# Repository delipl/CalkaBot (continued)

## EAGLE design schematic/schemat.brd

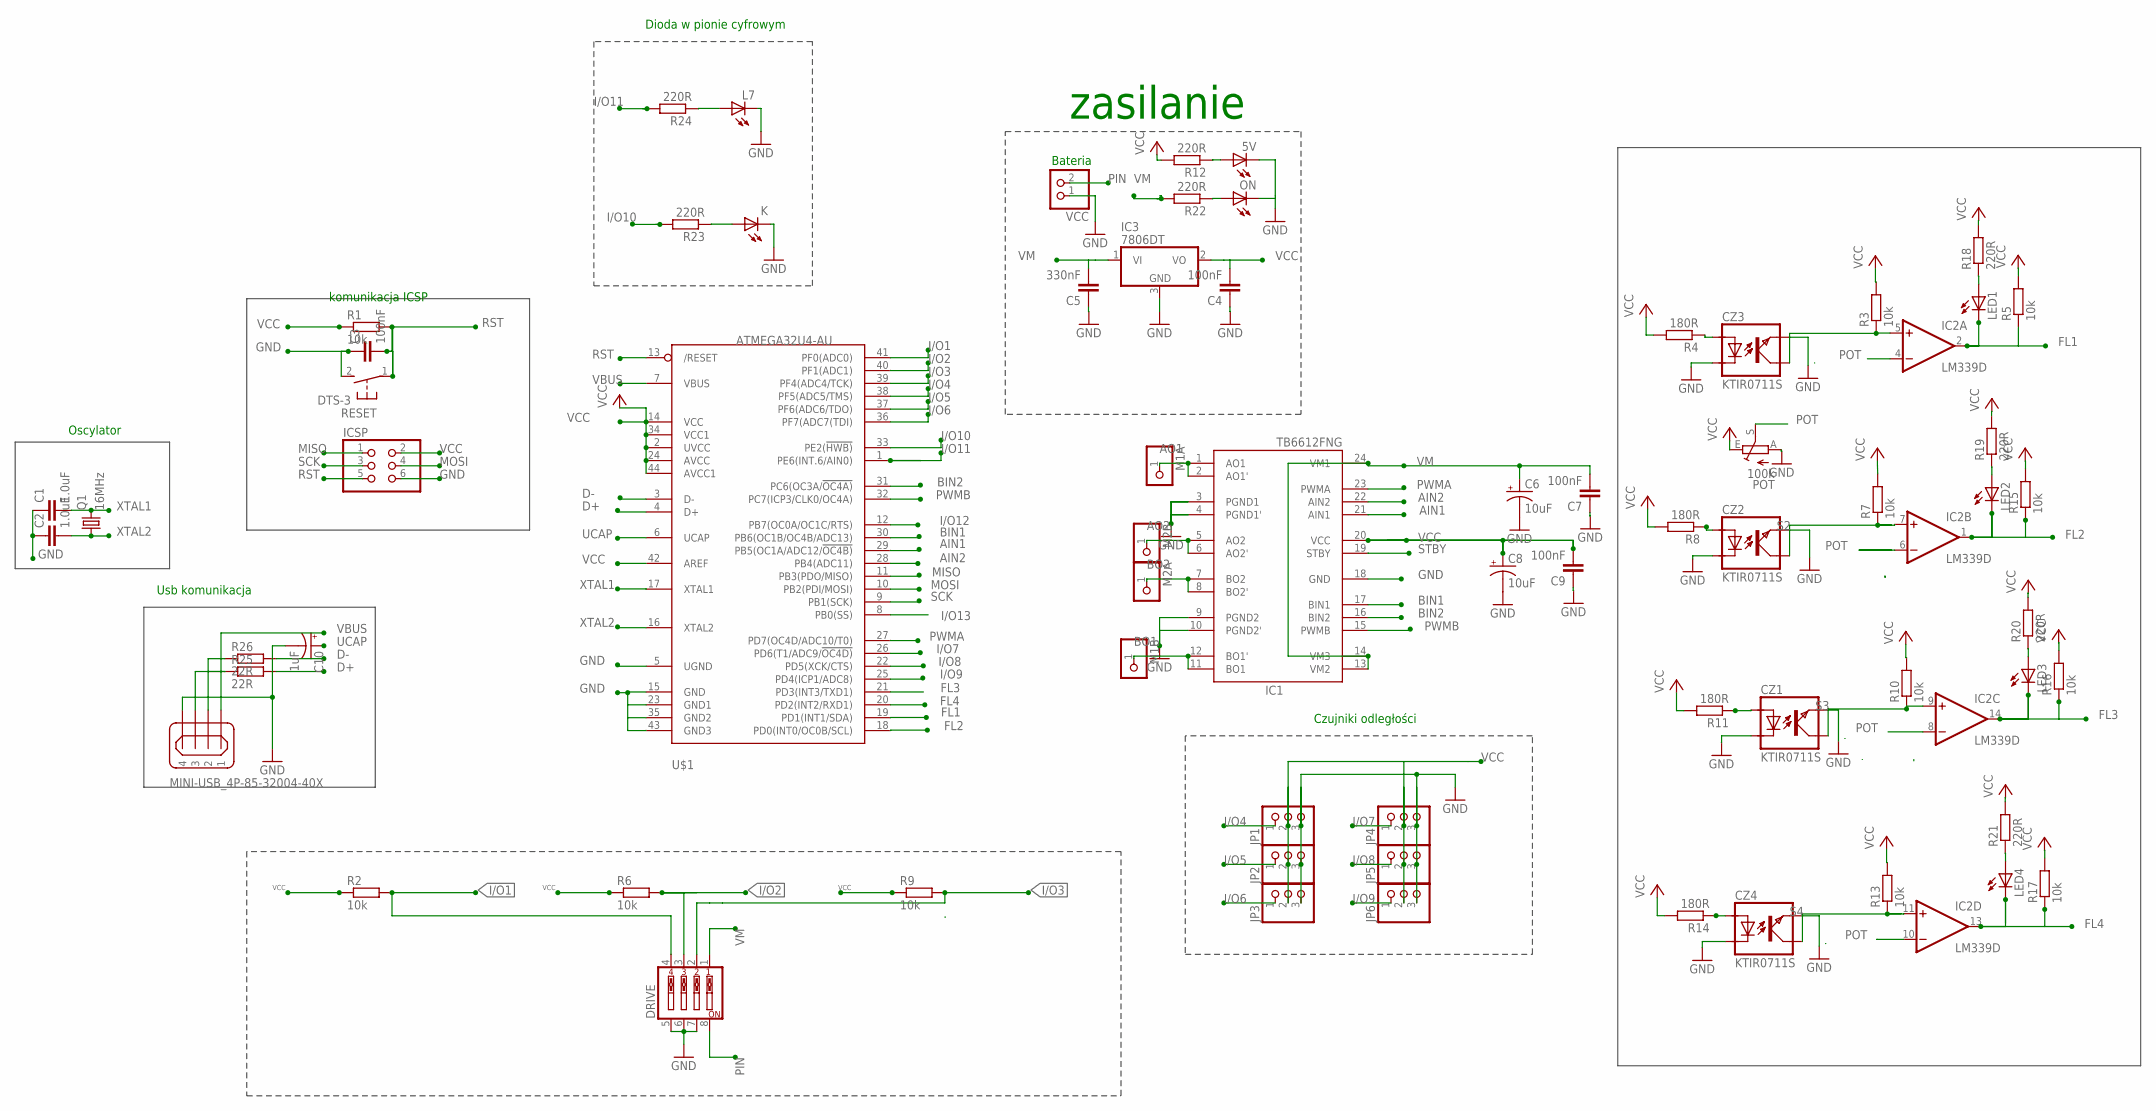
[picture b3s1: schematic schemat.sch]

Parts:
5V: LEDCHIP-LED0805; CHIP-LED0805
C1, C2: 1.0uF; C0805
C3, C4, C7, C9: 100nF; C0805
C5: 330nF; C0805
C6, C8: 10uF; UD-4X5,8_NICHICON
C10: 1uF; UD-4X5,8_NICHICON
CZ1, CZ2, CZ3, CZ4: KTIR0711S; TOP
DRIVE: SW_DIP-4; EDG-04
IC1: TB6612FNG; SSOP24
IC2: LM339D; SO14
IC3: 7806DT; TO252
ICSP: PINHD-2X3; 2X03
JP1, JP2, JP3, JP4, JP5, JP6: PINHD-1X3; 1X03
K: LEDCHIP-LED0805; CHIP-LED0805
L7: LEDCHIP-LED0805; CHIP-LED0805
LED1, LED2, LED3, LED4: LEDCHIP-LED0805; CHIP-LED0805
M1A, M1B, M2A, M2B: PINHD-1X1; 1X01
ON: LEDCHIP-LED0805; CHIP-LED0805
POT: 100k; CA6V
Q1: 16MHz; CSM-7X-DU
R1, R2, R3, R5, R6, R7, R9, R10, R13, R15, R16, R17: 10k; R0805
R4, R8, R11, R14: 180R; R0805
R12, R18, R19, R20, R21, R22, R23, R24: 220R; R0805
R25, R26: 22R; R0805
RESET: DTS-3
U$1: ATMEGA32U4-AU; TQFP44
USB: MINI-USB_4P-85-32004-40X; 85-32004-40X
VCC: PINHD-1X2; 1X02

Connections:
AIN1: IC1.21 (AIN1), U$1.29 (PB5(OC1A/ADC12/!OC4B))
AIN2: IC1.22 (AIN2), U$1.28 (PB4(ADC11))
AO1: IC1.1 (AO1), IC1.2 (AO1'), M1A.1
AO2: IC1.5 (AO2), IC1.6 (AO2'), M2B.1
BIN1: IC1.17 (BIN1), U$1.30 (PB6(OC1B/OC4B/ADC13))
BIN2: IC1.16 (BIN2), U$1.31 (PC6(OC3A/!OC4A))
BO1: IC1.11 (BO1), IC1.12 (BO1'), M1B.1
BO2: IC1.7 (BO2), IC1.8 (BO2'), M2A.1
D+: R25.2, U$1.4 (D+)
D-: R26.2, U$1.3 (D-)
FL1: IC2.2 (OUT), LED1.C, R5.1, U$1.19 (PD1(INT1/SDA))
FL2: IC2.1 (OUT), LED2.C, R15.1, U$1.18 (PD0(INT0/OC0B/SCL))
FL3: IC2.14 (OUT), LED3.C, R16.1, U$1.21 (PD3(INT3/TXD1))
FL4: IC2.13 (OUT), LED4.C, R17.1, U$1.20 (PD2(INT2/RXD1))
GND: 5V.C, C1.1, C2.1, C3.1, C4.1, C5.1, C6.-, C7.1, C8.-, C9.1, C10.-, CZ1.EMITER, CZ1.KATODA, CZ2.EMITER, CZ2.KATODA, CZ3.EMITER, CZ3.KATODA, CZ4.EMITER, CZ4.KATODA, DRIVE.5, DRIVE.6, DRIVE.7, IC1.3 (PGND1), IC1.4 (PGND1'), IC1.9 (PGND2), IC1.10 (PGND2'), IC1.18 (GND), IC2.12 (GND), IC3.3 (GND), ICSP.6, JP1.3, JP2.3, JP3.3, JP4.3, JP5.3, JP6.3, K.C, L7.C, ON.C, POT.A, RESET.2, U$1.5 (UGND), U$1.15 (GND), U$1.23 (GND1), U$1.35 (GND2), U$1.43 (GND3), USB.4, VCC.1
I/O1: DRIVE.4, R2.2, U$1.41 (PF0(ADC0))
I/O2: DRIVE.3, R6.2, U$1.40 (PF1(ADC1))
I/O3: DRIVE.2, R9.2, U$1.39 (PF4(ADC4/TCK))
I/O4: JP1.1, U$1.38 (PF5(ADC5/TMS))
I/O5: JP2.1, U$1.37 (PF6(ADC6/TDO))
I/O6: JP3.1, U$1.36 (PF7(ADC7(TDI))
I/O7: JP4.1, U$1.26 (PD6(T1/ADC9/!OC4D))
I/O8: JP5.1, U$1.22 (PD5(XCK/CTS))
I/O9: JP6.1, U$1.25 (PD4(ICP1/ADC8))
I/O10: R23.2, U$1.33 (PE2(!HWB))
I/O11: R24.2, U$1.1 (PE6(INT.6/AIN0))
I/O12: U$1.12 (PB7(OC0A/OC1C/RTS))
I/O13: U$1.8 (PB0(SS))
MISO: ICSP.1, U$1.11 (PB3(PDO/MISO))
MOSI: ICSP.4, U$1.10 (PB2(PDI/MOSI))
unnamed: CZ3.KOLEKTOR, IC2.5 (+IN), R3.1
unnamed: K.A, R23.1
unnamed: 5V.A, R12.1
unnamed: ON.A, R22.1
unnamed: R26.1, USB.2
unnamed: R25.1, USB.3
unnamed: LED1.A, R18.1
unnamed: CZ3.ANODA, R4.1
unnamed: LED2.A, R19.1
unnamed: LED3.A, R20.1
unnamed: LED4.A, R21.1
unnamed: L7.A, R24.1
unnamed: CZ2.ANODA, R8.1
unnamed: CZ1.ANODA, R11.1
unnamed: CZ4.ANODA, R14.1
PIN: DRIVE.8, VCC.2
POT: IC2.4 (-IN), IC2.6 (-IN), IC2.8 (-IN), IC2.10 (-IN), POT.S
PWMA: IC1.23 (PWMA), U$1.27 (PD7(OC4D/ADC10/T0))
PWMB: IC1.15 (PWMB), U$1.32 (PC7(ICP3/CLK0/OC4A))
RST: C3.2, ICSP.5, R1.2, RESET.1, U$1.13 (/RESET)
S2: CZ2.KOLEKTOR, IC2.7 (+IN), R7.1
S3: CZ1.KOLEKTOR, IC2.9 (+IN), R10.1
S4: CZ4.KOLEKTOR, IC2.11 (+IN), R13.1
SCK: ICSP.3, U$1.9 (PB1(SCK))
STBY: IC1.19 (STBY)
UCAP: C10.+, U$1.6 (UCAP)
VBUS: U$1.7 (VBUS), USB.1
VCC: C4.2, C8.+, C9.2, IC1.20 (VCC), IC2.3 (V+), IC3.2 (VO), ICSP.2, JP1.2, JP2.2, JP3.2, JP4.2, JP5.2, JP6.2, POT.E, R1.1, R2.1, R3.2, R4.2, R5.2, R6.1, R7.2, R8.2, R9.1, R10.2, R11.2, R12.2, R13.2, R14.2, R15.2, R16.2, R17.2, R18.2, R19.2, R20.2, R21.2, U$1.2 (UVCC), U$1.14 (VCC), U$1.24 (AVCC), U$1.34 (VCC1), U$1.42 (AREF), U$1.44 (AVCC1)
VM: C5.2, C6.+, C7.2, DRIVE.1, IC1.13 (VM2), IC1.14 (VM3), IC1.24 (VM1), IC3.1 (VI), R22.2
XTAL1: C1.2, Q1.2, U$1.17 (XTAL1)
XTAL2: C2.2, Q1.1, U$1.16 (XTAL2)

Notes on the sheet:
Oscylator
Usb komunikacja
komunikacja ICSP
Bateria
zasilanie
Dioda w pionie cyfrowym
Czujniki odległości

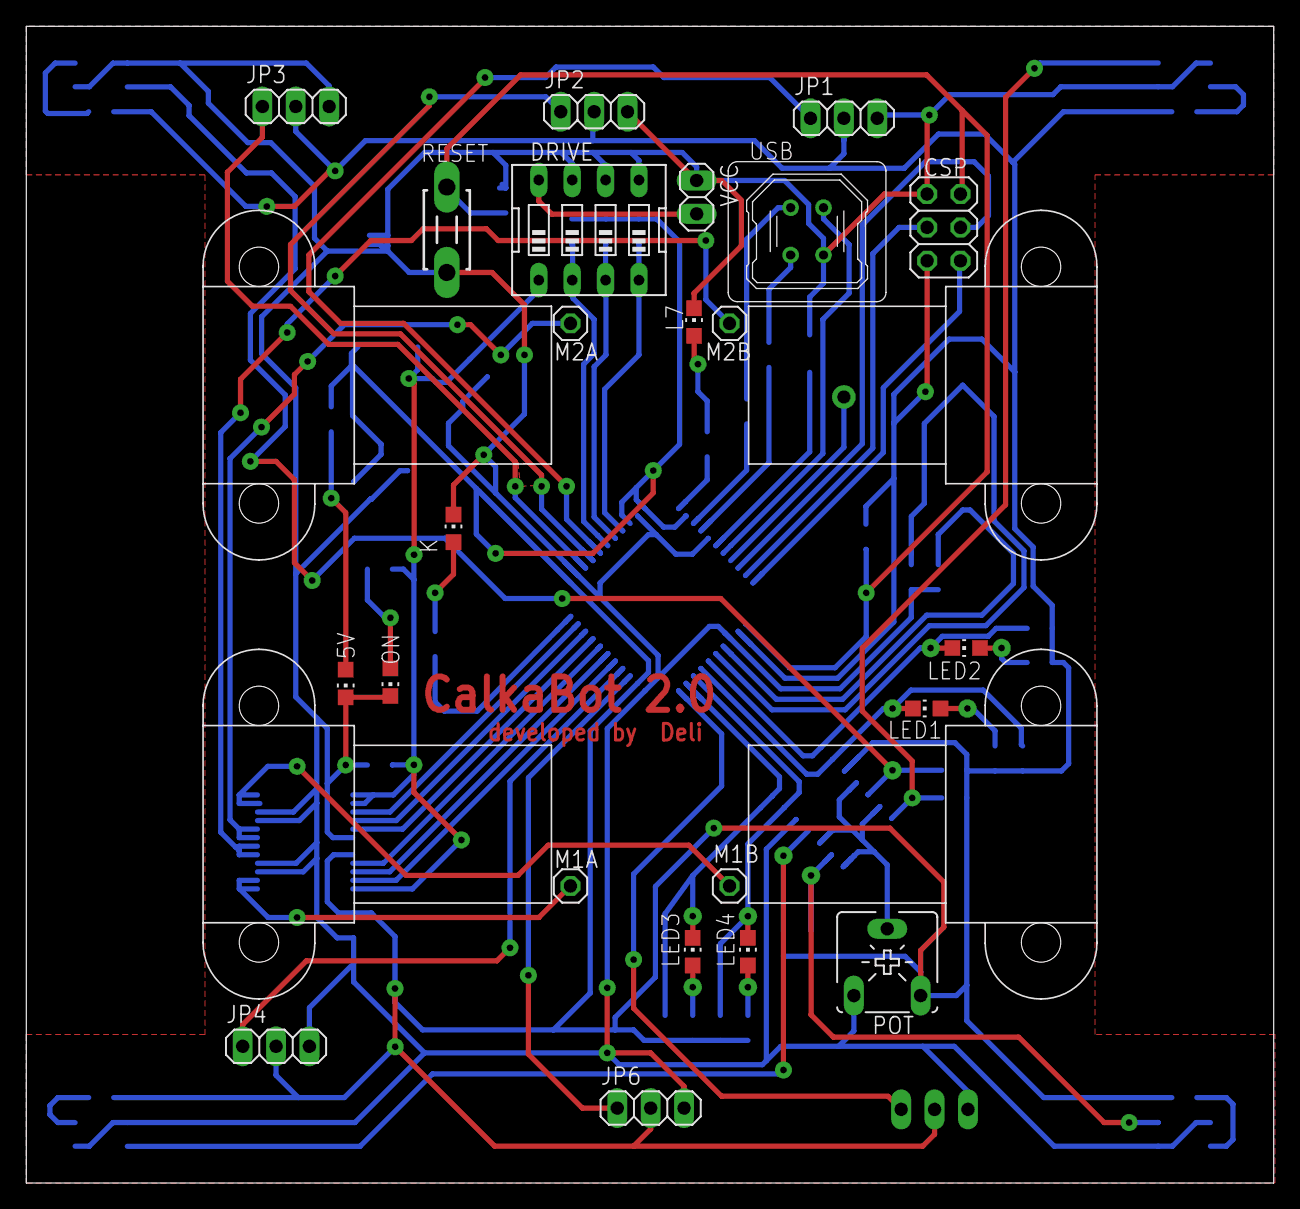
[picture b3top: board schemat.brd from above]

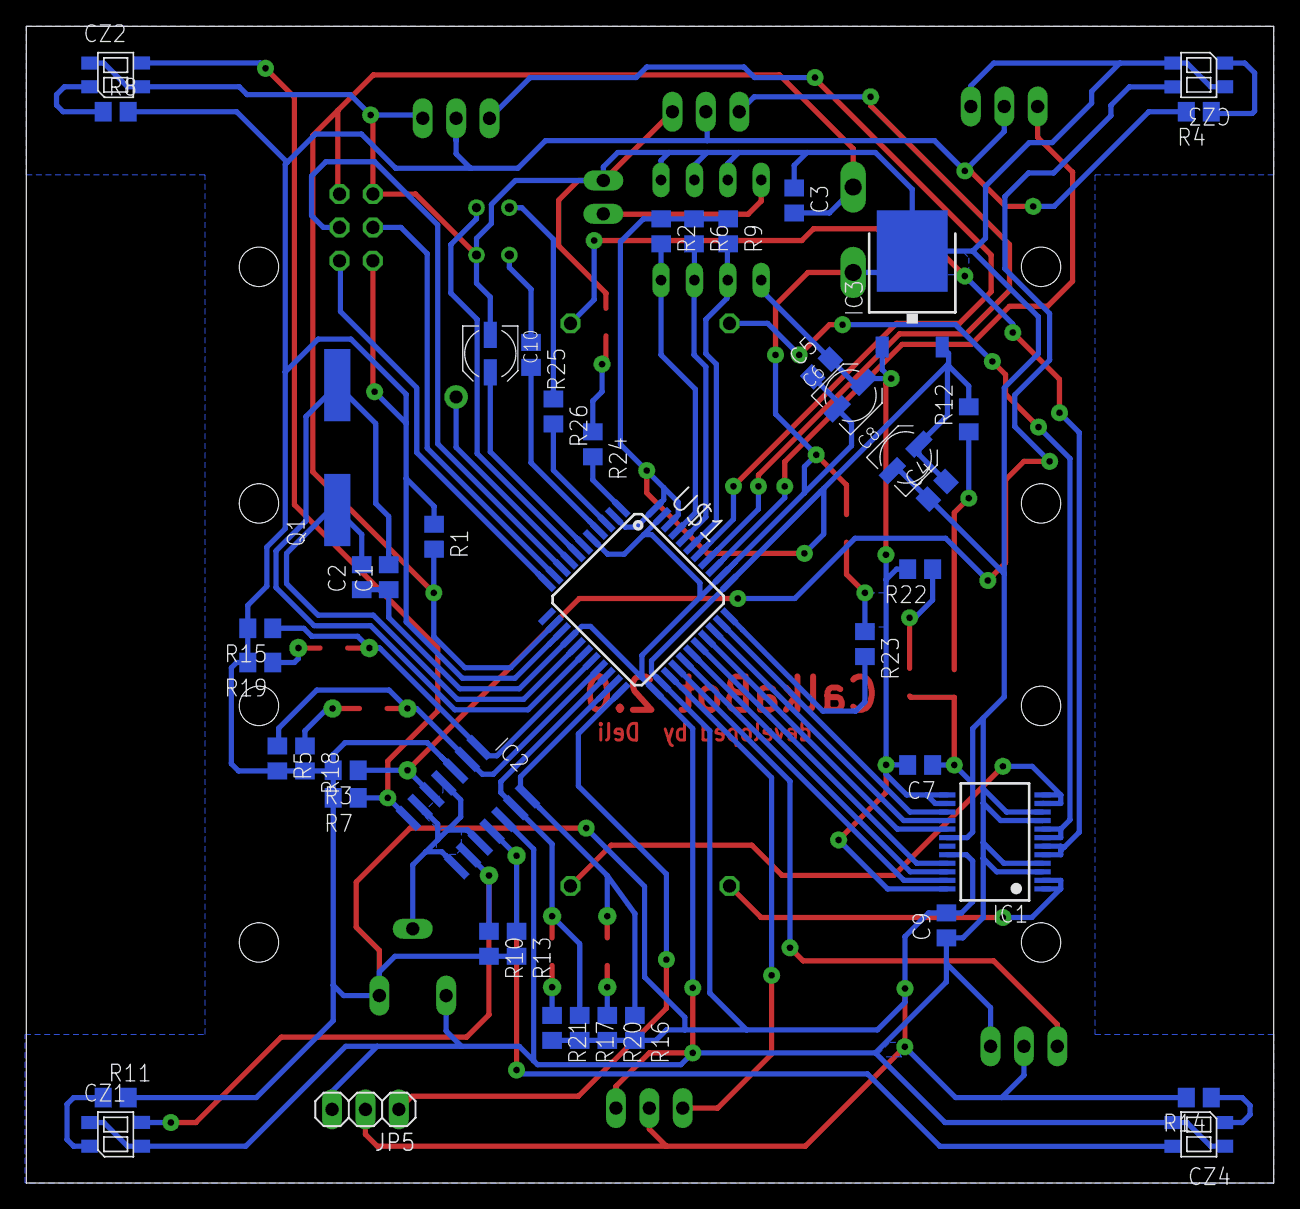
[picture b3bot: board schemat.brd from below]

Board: 2 copper layers, 94.9 x 88.0 mm, 73 parts (46 on the bottom side), 58 nets.

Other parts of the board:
U$6, U$7, U$8, U$9: HP_NM

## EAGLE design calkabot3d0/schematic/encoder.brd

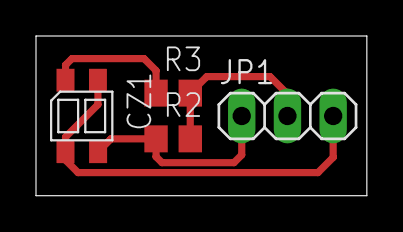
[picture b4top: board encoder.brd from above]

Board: 2 copper layers, 18.4 x 8.9 mm, 4 parts (0 on the bottom side), 4 nets.

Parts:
CZ1: KTIR0711S; TOP
JP1: 1X03
R2: 20k; R0805
R3: 200; R0805

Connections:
unnamed: CZ1.EMITER, CZ1.KATODA, JP1.3
unnamed: CZ1.KOLEKTOR, JP1.1, R2.1
unnamed: CZ1.ANODA, R3.1
unnamed: JP1.2, R2.2, R3.2

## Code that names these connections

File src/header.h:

#include <Arduino.h>
#include "../lib/IRremote/IRremote.h"



uint8_t full 		= 255;
uint8_t optimal = 200; //max speed, not to fligh away from ring
uint8_t half 		= 180;
uint8_t program = 0x0;
bool first 			= 0b1;		//first loop after start
bool shown 			= false;
bool touch 			= false;
bool checkFloor = true;
int p = 50;
unsigned long start;

	//direction
	bool direction = true;
	#define direction_TOG direction ^= true // 0 ^ 1 = 1 1

  //Leds on board
	#define builtLed1 		(1<<PE2)
	#define builtLed2		  (1<<PE6)
	#define builtLed1_ON	PORTE |= builtLed1  	// |0000| | 0001 = |0001|
	#define builtLed2_ON	PORTE |= builtLed2
	#define builtLed1_OFF	PORTE &= ~builtLed1 	// |0001| & ~0001 = 0001 & 1110 = |0000|
	#define builtLed2_OFF	PORTE &= ~builtLed2
	#define builtLed1_TOG	PORTE ^= builtLed1 		// |0000| ^ 0001 = |0001|
	#define builtLed2_TOG	PORTE ^= builtLed2 		// |1000| ^ 1000 = |0000|

  //floor sensors
  #define FaR 			(1<<PD0)
  #define FaL				(1<<PD1)
  #define FbR				(1<<PD3)
  #define FbL				(1<<PD2)

  #define edgeA     ((PIND & FaL) | (PIND & FaR))
  #define edgeB     ((PIND & FbL) | (PIND & FbR))
  #define edgeAL    (PIND & FaL)
  #define edgeAR    (PIND & FaR)
  #define edgeBL    (PIND & FbL)
  #define edgeBR    (PIND & FbR)

  //buttons
  #define but1      (1<<PF4)
  #define but2      (1<<PF1)
  #define but3      (1<<PF0)

	#define status_but1	(PINF & but1)
	#define status_but2	(PINF & but2)
	#define status_but3 (PINF & but3)

	//ir comunication
	//#define irPin     		(1<<PB0)
	#define irPin     		17
	#define irPin_status	(PINB & irPin)
	IRrecv irrecv(irPin);
	decode_results results;

  //distans Sensors
  #define IRa       (1<<PF6)
  #define IRaR      (1<<PF5)
  #define IRaL      (1<<PF7)
  #define IRb       (1<<PD4)
  #define IRbR      (1<<PD5)
  #define IRbL      (1<<PD6)

  #define disA      (PINF & IRa)
  #define disAR     (PINF & IRaR)
  #define disAL     (PINF & IRaL)
  #define disB      (PIND & IRb)
  #define disBR     (PIND & IRbR)
  #define disBL     (PIND & IRbL)

  //control motor A PB
	#define Ma1				(1<<PB5)
	#define Ma2				(1<<PB4)
	#define MaPWM			(1<<PD7)

	#define Ma1_ON		PORTB |= Ma1
	#define Ma2_ON	 	PORTB |= Ma2
	#define Ma1_OFF		PORTB &= ~Ma1
	#define Ma2_OFF	 	PORTB &= ~Ma2
	#define	MaPWM_ON	PORTD |= MaPWM

  //control motor B
  #define Mb1				(1<<PB6)
  #define Mb2				(1<<PC6)
  #define MbPWM			(1<<PC7)

	#define Mb1_ON		  PORTB |= Mb1
	#define Mb2_ON	 		PORTC |= Mb2
	#define Mb1_OFF		  PORTB &= ~Mb1
	#define Mb2_OFF	 		PORTC &= ~Mb2
	#define	MbPWM_ON		PORTC |= MbPWM

	//show error function
	void error(int errorNr){
		Ma1_OFF;
		Ma2_OFF;
		Mb1_OFF;
		Mb2_OFF;
		while(true){
			for (int i = 0; i < errorNr; ++i){
				delay(200);
				builtLed1_ON;
				delay(200);
				builtLed1_OFF;
			}
			delay(2000);

			//Serial.println(program);
		}
	}

	//if touch
	bool floorSensors(){
 		if(direction)					return !edgeAL || !edgeAR;
		else if(!direction)  	return !edgeBR || !edgeBL;
		else error(15);
		return 0;
	}

	//pins ins and outs
  void pins(){
    //output ports for motor A control
		pinMode(6, OUTPUT);
    DDRB |= Ma1 | Ma2;
		DDRD |= MaPWM;
		MaPWM_ON;
    //output ports for motor B control
  	DDRC |= Mb2;
    DDRB |= Mb1;
		DDRC |= MbPWM;
		MbPWM_ON;
		pinMode(13, OUTPUT);

		//output ports for leds
  	DDRE |= builtLed1 | builtLed2;

  	//input ports floor sensor
    DDRD 	&= ~FaR & ~FaL & ~FbR & ~FaL;
    //disconnect inside VCC
    PORTD &= ~FaR & ~FaL & ~FbR & ~FaL;

    //input ports for buttons
    DDRF  &= ~but1 & ~but2 & ~but3;
    //disconnect insice VCC
    PORTF &= ~but1 & ~but2 & ~but3;

		//input port for ir
		DDRB 	&= ~irPin;
		//disconnect inside VCC
		PORTB &= ~irPin;

    //input portys for distans sensors
    DDRF &= ~IRa & ~IRaR & ~IRaL;
    DDRD &= ~IRb & ~IRbR & ~IRbL;
    //disconect inside VCC
    PORTF &= ~IRa & ~IRaR & ~IRaL;
    PORTD &= ~IRb & ~IRbR & ~IRbL;
  }



	//diode start
	void showStart(){
		builtLed1_ON;
		for (int i = 0; i < 5; ++i){
			delay(100);
			builtLed1_TOG;
	    builtLed2_TOG;
		}
		builtLed1_OFF;
		builtLed2_OFF;
	}

	//when CalkaBot sees the enemyy not straight ahead
	bool seeEnemy(){
	  return  !disAR  ||
	          !disAL  ||
	          !disBR  ||
	          !disBL	||
						!disA		||
						!disB;
	}


	byte irRemoute ()
	{
	byte dane=0;
	  while(dane==0)
	{
	   if (irrecv.decode(&results)) // sprawdza, czy otrzymano sygna� IR
	{
	       unsigned long odczyt = results.value; // sygnał zapisuje jako odczyt
	switch (odczyt)
	       {
	case 3785549847: //power
	  dane = 1;
	break;
	case 1857: //power
	  dane = 1;
	break;
	case 3905: //eneter
		dane = 1;
	break;
	case 16711935: //eneter
		dane = 1;
	break;

	default:
	         dane=0;
	}
	      irrecv.resume(); // reseruje czujnik
	}
	   else
	{
	    dane=0;
	}
	  }
	return dane ;
	}

	bool readButton(){
		if (!digitalRead(irPin)){
			delay(100);
			if(!digitalRead(irPin)){

				return false;
			}else return true;
		}else return true;
		return true;
	}

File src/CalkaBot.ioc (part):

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Mcu.Name=STM32F103C(8-B)Tx
Mcu.Package=LQFP48
Mcu.UserName=STM32F103C8Tx
PA1.GPIOParameters=GPIO_Label
PA1.GPIO_Label=PWMA
PA1.Signal=S_TIM2_CH2
PA11.Mode=Device
PA11.Signal=USB_DM
PA12.Mode=Device
PA12.Signal=USB_DP
PA13.Mode=Serial_Wire
PA13.Signal=SYS_JTMS-SWDIO
PA14.Mode=Serial_Wire
PA14.Signal=SYS_JTCK-SWCLK
PA2.GPIOParameters=GPIO_Label
PA2.GPIO_Label=Ma2
PA2.Signal=GPIO_Output
PA3.GPIOParameters=GPIO_Label
PA3.GPIO_Label=Ma1
PA3.Signal=GPIO_Output
PA4.GPIOParameters=GPIO_Label
PA4.GPIO_Label=STBY
PA4.Signal=GPIO_Output
PA5.GPIOParameters=GPIO_Label
PA5.GPIO_Label=Mb1
PA5.Signal=GPIO_Output
PA6.GPIOParameters=GPIO_Label
PA6.GPIO_Label=Mb2
PA6.Signal=GPIO_Output
PA7.GPIOParameters=GPIO_Label
PA7.GPIO_Label=PWMB
PA7.Signal=S_TIM3_CH2
PB10.GPIOParameters=GPIO_Label
PB10.GPIO_Label=DIS_R
PB10.Signal=GPIO_Input
PB11.GPIOParameters=GPIO_Label
PB11.GPIO_Label=DIS_L
PB11.Signal=GPIO_Input
PB4.GPIOParameters=GPIO_Label
PB4.GPIO_Label=INT
PB4.Signal=GPXTI4
PB6.Mode=I2C
PB6.Signal=I2C1_SCL
PB7.Mode=I2C
PB7.Signal=I2C1_SDA
PC13-TAMPER-RTC.GPIOParameters=PinState,GPIO_Label
PC13-TAMPER-RTC.GPIO_Label=LED_BUILTIN
PC13-TAMPER-RTC.PinState=GPIO_PIN_SET
PC13-TAMPER-RTC.Signal=GPIO_Output
PD0-OSC_IN.Mode=HSE-External-Oscillator
PD0-OSC_IN.Signal=RCC_OSC_IN
PD1-OSC_OUT.Mode=HSE-External-Oscillator
PD1-OSC_OUT.Signal=RCC_OSC_OUT
RCC.SYSCLKFreq_VALUE=48000000
RCC.SYSCLKSource=RCC_SYSCLKSOURCE_PLLCLK
board=custom

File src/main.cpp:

#include "header.h"

void setup(){

	irrecv.enableIRIn();
	//czujniki odległości
	pinMode(sensorF, INPUT);
	pinMode(sensorFL, INPUT);
	pinMode(sensorFR, INPUT);
	pinMode(sensorB, INPUT);
	pinMode(sensorBR, INPUT);
	pinMode(sensorBL, INPUT);

	//silnik
	pinMode(AIN1, OUTPUT);
	pinMode(AIN2, OUTPUT);
	pinMode(BIN1, OUTPUT);
	pinMode(BIN2, OUTPUT);

	//Led
	pinMode(9, OUTPUT);
	digitalWrite(9,HIGH);

	for(int i = 0; i < 5; i++){
		digitalWrite(9, 0);
		delay(100);
		digitalWrite(9, 1);
		delay(100);
	}
}



void loop(){
bool play=1;
byte check = irRemoute();
 if (check != 0)
{
	play=1;
  // Tutaj podajemy co ma wykonać dalej z zmienną check jeżeli nie jest ona zerem
}
//play=1;
while(play){//nzfs
		while (true){
			if(!floor()){
				while(digitalRead(sensorB)==0) go(0, 0);
				while(digitalRead(sensorF)==0) go(0, 1);
				if(digitalRead(sensorFR)==0) go(3, 1);
				else if(digitalRead(sensorFL)==0) go(2, 1);
				else if(digitalRead(sensorBR)==0) go(3, 0);
				else if(digitalRead(sensorBL)==0) go(2, 0);
				else spin();
			}else if(floorFront()){
				go(0, 0);
				delay(100);
			}else if(floorBack()){
				go(0, 1);
				delay(100);
			}
		}
 	}

}

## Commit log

2018-10-02 init
2018-10-02 copied Eagle project
2018-10-02 added README.dm
2018-10-03 added resonator
2018-10-21 Powiększone dziurki
2018-11-07 przyciski i usunalem isp
2018-11-08 Dodałem stabilizator i filtrację stabilizator i przyciski
2018-11-08 Dodałem filtr do zasialania silników i do sterownika
2018-11-08 podłączenie przycisków
2018-11-08 podłączenie przycisków teraz
2018-11-16 nie ma miejsca na usb, pcb prawie skończone
2018-11-16 potrzebne wyjscia do czujnikow odleglosci i płytka z gniazdem usb
2018-11-21 niezapisane rzeczt
2018-11-22 dodalem dipy
2018-11-22 połączono wszystkie VCC i GND
2018-11-22 dodano diode
2018-11-22 chyba skończyłem
2018-11-22 end 2x
2018-11-22 end 3x
2018-11-22 nie zmargowałem z squash :,(
2018-11-22 dodałem sobie XD
2018-11-26 revert
2018-12-08 nie wychodzi...
2018-12-08 poprawki wprowadzone, zmiana dipa z 3 na 4, przesunięcie włącznika zasilania
2018-12-09 dodałem gniazdo B, włącznik przyłączony z trybami
2018-12-09 usunąłem pdfy
2018-12-09 zapomiałem o ziemi
2018-12-09 Cały robot z kołami, redukcja miejsca
2018-12-09 redukcja miejsca, przygotowywanie pod dodawnie transoptora smd
2018-12-09 dodałem koła i poczne ściany
2018-12-09 nie starcza mi miejsca nie wiem o co cmon
2018-12-09 zapis
2018-12-09 test
2018-12-09 test2
2018-12-09 Mogę już podłączyć na transoptory
2018-12-09 jeszcze coś się nie zapisało
2018-12-10 Podłączone transoptory, trzeba rozkminić jak podłączyć gniazda
2018-12-13 przesunięte ścieżki i elementy żeby nie zasłaniały silniki
2018-12-13 Ładnie opisane od góry
2018-12-13 dodane pinheady dla czujników odległości, teraz trzeba je podłączyć
2018-12-25 tylko rozmieściłem
2019-01-12 jakies niezkomitowane rzeczy xD
2019-01-23 polaczenia plytki skonczone teraz tylko poligony
2019-01-23 dodanie wymiarow
2019-01-23 porobione paddingi
2019-01-23 poligony*
2019-02-04 plytka skonczona zrobione poligony
2019-02-04 dodalem pdfy
2019-02-04 niezapisane zmieny :D
2019-02-04 zmiana nazwy folderu
2019-03-03 powiekszylem pierscien viasow
2019-03-03 zmiana viasow na 0.5/1.3
2019-03-24 init dodanie tabeli z pinoutem
2019-04-01 Wypełnianie Dokumentacji
2019-04-07 tabela avr
2019-04-07 enter po tytule tabeli
2019-04-07 zamiana miejscami w dokumentacji
2019-04-07 init code.ino
2019-04-07 Zamienilem na hexy
2019-04-09 sterowania silnika do przodu i do tyłu
2019-04-10 zmiana ide na platformio na atomie, zamiana pliku code.ino na main.cpp
2019-04-10 dodanie ladnych zmiennych
2019-04-18 poprawa wyglądu schematu
2019-04-19 dodanie header.h wszystkie #define funkcje main.cpp
2019-04-19 Literówki, kompiluje się
2019-04-19 bez elsa ponieważ dojeżdzałby za każdym razem do krawędzo
2019-04-19 pinMode przed Ledami
2019-04-19 Jedzie
2019-04-19 Pwm fix, usb dla windowsa
2019-04-20 Sprawdzanie switchy i podzial na podprogramy
2019-04-20 dodano funkcje error (wymiguje numer błędu)
2019-04-20 pierwszy error(i chyba ostatni ale moze sie przyda potem)
2019-04-20 core wiekszosci programow ktore bedziemy robic i kilka funkcji
2019-04-21 linux platform.io
2019-04-21 dodanie plików backupowych z eagle do .gitignore
2019-04-21 usunięcie backupow
2019-04-21 oscylatop + ISP
2019-04-21 Naprawienie i poprawa odczytu przełączników
2019-04-21 Sterowanie silnikami przeniesione do motro.h
2019-04-21 Jak umiemy C to dodałem direction_TOG zamiast funkcji togDirection();
2019-04-21 Złe przypisanie zmiennej
2019-04-22 Usunięcie syfu z mainu, przeniesienie floorSensors() do motor.h, przepisanie program0(), dodanie toSeeFront()
2019-04-22 komentarz do programu 0
2019-04-22 Dodanie pierwszego loopa `first` Dodanie `program2()` Dodanie funkcji `spin()`
2019-04-24 Zmiana programatora na USBasp Naprawnie funkcji `error()` Dodanie kolejnych plików kolejnych programów
2019-04-24 i jeszcze program7.h
2019-04-24 przygotowanie programów do pisania
2019-04-24 Przeniesienie programów do programs/
2019-04-24 showStart() przeniesienie czujnikow do header
2019-04-24 zmiana pwm w silnikach
2019-04-24 podstawowe wypelnienie programow
2019-04-24 programy
2019-04-24 program 1
2019-04-24 program 2 i drobna poprawa programu 1
2019-04-24 program 3
2019-04-24 program 7
2019-04-24 program 4 and improved program 2
2019-04-25 basic program dziala jak pod wiedniem
2019-04-25 a teraz to takie dziala ze hunyadi bylby dumny
2019-04-25 spinner taki co powinien dzialac
2019-04-25 nie testowany linefolowwer
2019-04-25 noc przed zawodami
2019-04-25 dodano slowSpin() linefloower moze dziala ale Rudy nie chce dać robota #polRegio
2019-04-27 jezdzi po ziei
2019-04-27 dodano zmienną `checkFloor` - aktywuje ona czujniki podłoza
2019-04-29 zmienilem ify na while i dalem errora na 5(pusty program)
2019-04-29 opis programu 6
2019-05-12 zmiiana skrecania
2019-05-13 lib/ w .gitignore
2019-05-13 dodano czujnik IR
2019-05-14 Podstawowy program na program6()
2019-05-14 spin() w program5()
2019-05-15 zmiana portu ir
2019-05-15 dzialajacy seeFront na tyl w program2()
2019-05-15 ify na while i dodany przod
2019-05-17 poprawnie odpala sie program z pilota i zatrzymuje z przycisku program2() spin program3() skan mapy
2019-05-17 dodano waitera
2019-05-17 zmiana programow w readme
2019-05-20 przeniesienie plikow do calkabot2
2019-05-20 dodanie calkabot1 do repo
2019-05-20 zmiana .gitignore
2019-05-21 zmiana README
2019-05-21 dodano .gitignore do .gitignore
2019-05-21 testowa spacja dlagita :)
2019-05-21 wyczyszczenie programów
2019-05-21 zmiana kodu na C zakmentowanie IR
2020-04-06 init calakabot3.0
2020-04-23 Posegregowanie projektu, rozdzielienie robotów na dwie wersje
2020-05-17 ignoracja
2020-05-17 teraz schemat wygląda ładnie
2020-09-29 Jtag ssie, zrobiłem SWD. Zmiana płyki. pomniejszenie dodanie resetu itd.
2020-10-05 inicjacja projektu
2020-10-05 How to program BluePill via USB
2020-10-06 Add instructions to READE
2020-10-06 Adding working platformio.ini file on linux
2020-10-06 Ignore platformio.ini
2020-10-06 Distans sensor work
2020-10-07 Adding I2C pull-up resistors, 5V on board, change package for LM1117, PB2 (BOOT1) short to GND
2020-10-08 Adding motor outputs
2020-10-08 Change board
2020-10-09 Initial commit of simulation
2020-10-10 EAGLE WORKING ON LINUX!
2020-10-10 Basic display objects
2020-10-10 Add classes and rotation
2020-10-10 that looks much better
2020-10-11 add (not the best) movement
2020-10-11 Adding random values generator and implement this into main.py
2020-10-11 add varibles and fix bug
2020-10-11 read random values to file
2020-10-11 remove additional file
2020-10-11 added battery voltage checker and led
2020-10-11 added switch to disconnect voltage from sensors
2020-10-11 comments on schematic, added led for I2C supply
2020-10-12 Linking in arduino works only with .h files,
2020-10-12 Acceleromoeter works fine
2020-10-12 Accelerometer shows angle thanks to example for MPU6050 from https://github.com/jrowberg/i2cdevlib
2020-10-12 Added schematic for encoder
2020-10-13 pcb design
2020-10-13 Change speed to street ;)
2020-10-13 dzięki działa adam jest słabu
2020-10-14 Add file reading with bugs
2020-10-14 Fix angle from global to local
2020-10-14 Fix not dissapearing robot
2020-10-14 Add movement animation
2020-10-14 reorganize code
2020-10-14 Change git ignore
2020-10-14 shit to ignore
2020-10-14 fixed .gitignere
2020-10-14 delete
2020-10-14 git ignore
2020-10-14 fixes
2020-10-14 update README.md
    new member
2020-10-14 lol adam na dól
2020-10-15 change code accoding to the prototype of 3d0
2020-10-15 Add motor files
2020-10-19 added 2
2020-10-19 Graphs added, looking for extrems doenst work
2020-10-20 dynamic reading values from file
2020-10-21 program finds maksimas
2020-10-31 Working program. Waiting for harware.
2020-10-31 ignore VS files
2020-10-31 ignore
2020-10-31 Release CalkaBot v1
2020-10-31 Release CalkaBot v2.0
2020-10-31 Repo for calkabot 3d0
2020-10-31 Tips
2020-10-31 Ignoring .vscode
2020-10-31 Change unused value
2020-11-04 Add in series stabilisators
2020-11-06 Goodbye Arduino
2020-11-07 added stm32IDE files
2020-11-07 only schema
2020-11-07 clear schema
2020-11-09 added charger, and over charge protection
2020-11-09 Added battery managment and motor drivers
2020-11-09 added MPU6050 to board, and two motor drivers
2020-11-09 new board
2020-11-11 3 ifs program
2020-11-12 smieci
2020-11-13 SD Card added
2020-11-16 Added piheads for sensors. Added transoptors.
2020-11-16 Pull up resistors to two I2C buses
2020-11-16 Feature update
2020-11-16 ułożenie pinów i podpięcie sterowników rage quit
2020-11-26 Reading I2C
